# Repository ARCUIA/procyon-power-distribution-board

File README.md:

# procyon-power-distribution-board
Power distribution board responsible for managing power for the Atlas flight controller, up to 3 FPV camera + VTX systems, a radio module, and a DC motor. Toggle-able camera power to save battery. Support for High-side switching, allowing for chassis grounding on VTX modules.

### V1 Typical Application
- Battery: 2S LiPo 5000 mAh
- Flight Controller: Atlas V3
     - Input Voltage: 5V
     - Inpue Current (max): 250 mAh
- Motor: BLDC RS-380SH-4535
     - Input Voltage: 5V
     - Input Current: <1 amp
- Radio: RFD900X
     - Input Voltage: 5V
     - Input Current: 1 amp
- FPV Systems: CADDX Walksnail Avatar HD Pro
     - Input Voltage: Battery (Minimum 6V)
     - Input Current: 0.5-1 amp

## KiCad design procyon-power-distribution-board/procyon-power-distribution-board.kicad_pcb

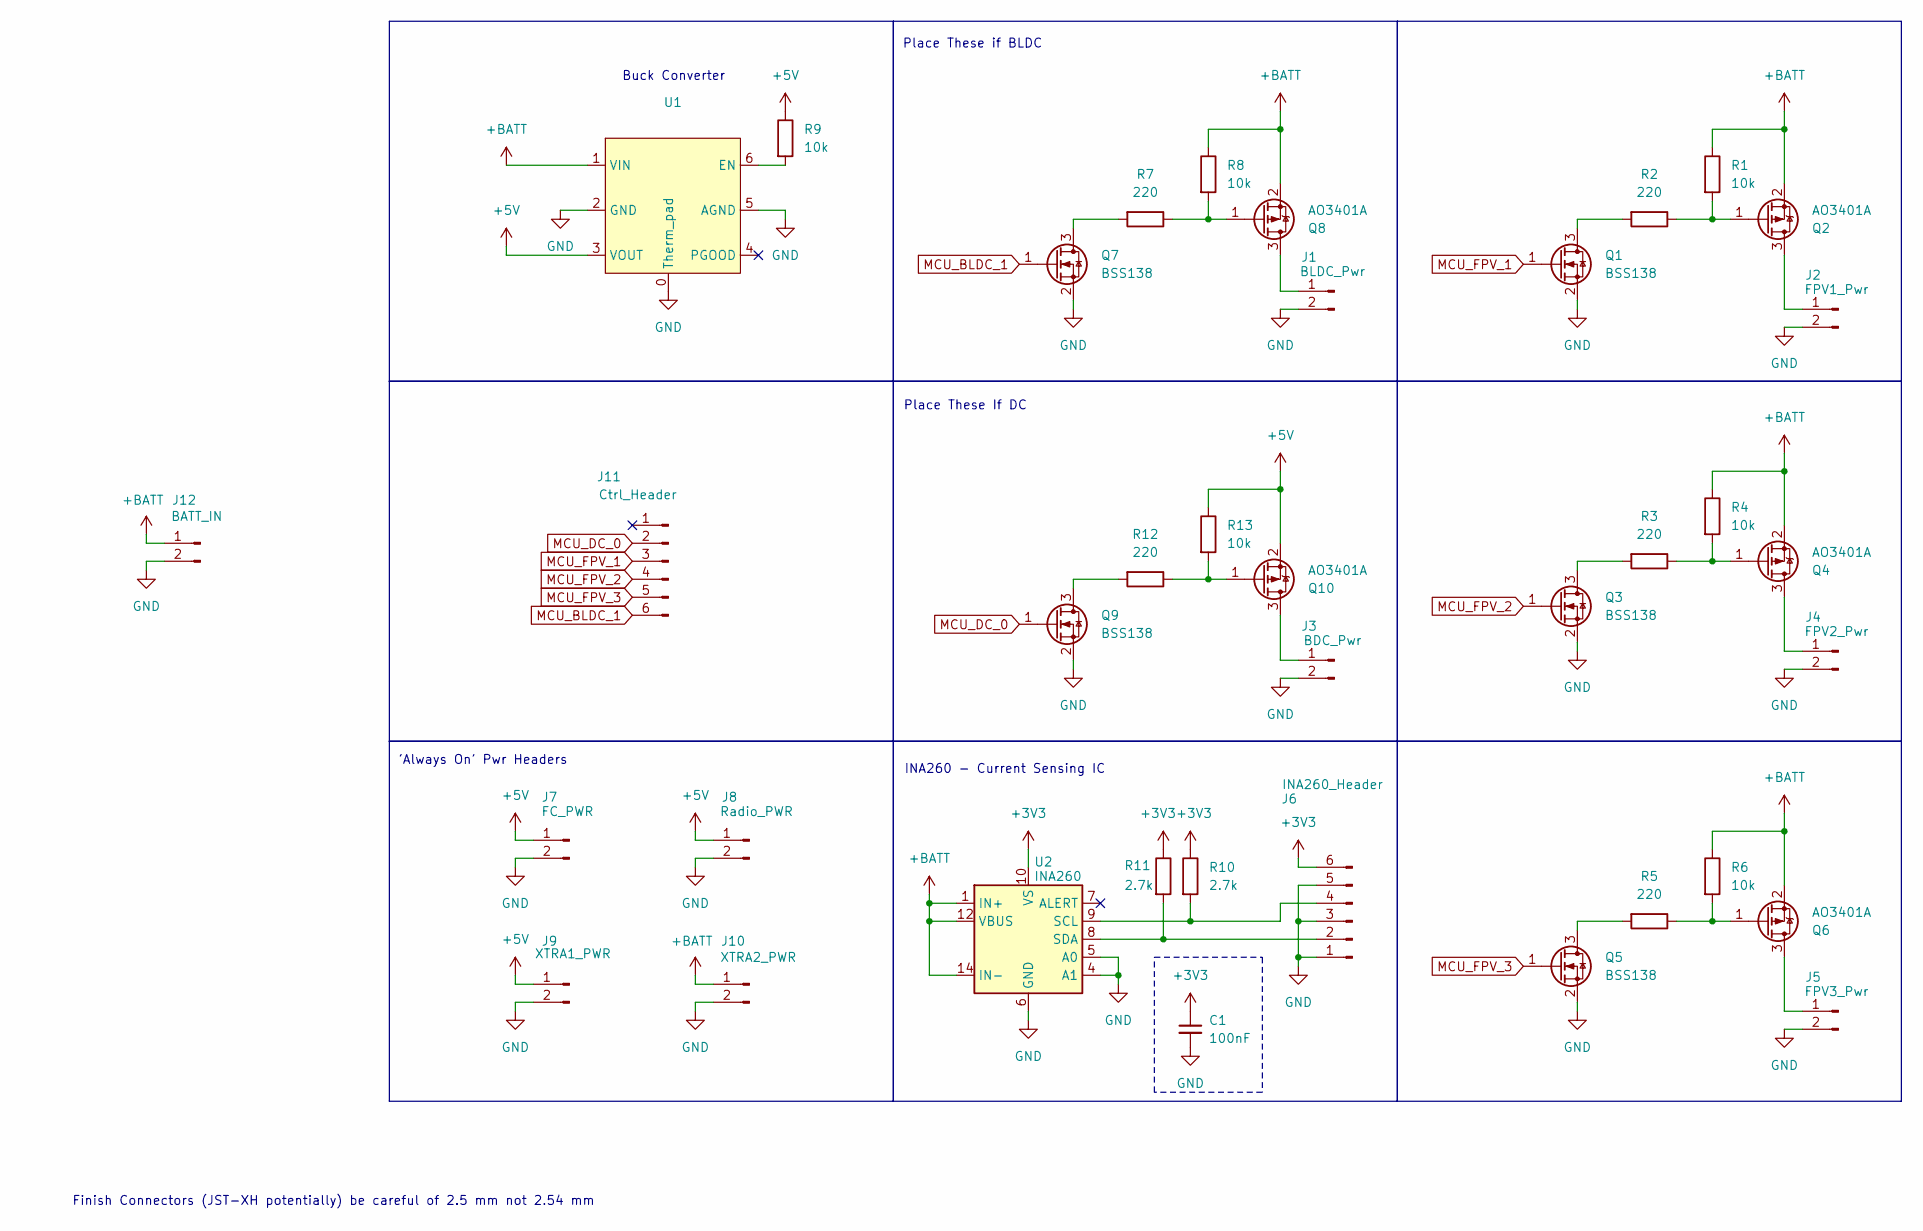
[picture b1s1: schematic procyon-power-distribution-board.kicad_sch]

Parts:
C1: 100nF; C_0603_1608Metric_Pad1.08x0.95mm_HandSolder
J1: BLDC_Pwr; JST_XH_S2B-XH-A-1_1x02_P2.50mm_Horizontal
J2: FPV1_Pwr; JST_XH_S2B-XH-A-1_1x02_P2.50mm_Horizontal
J3: BDC_Pwr; JST_XH_S2B-XH-A-1_1x02_P2.50mm_Horizontal
J4: FPV2_Pwr; JST_XH_S2B-XH-A-1_1x02_P2.50mm_Horizontal
J5: FPV3_Pwr; JST_XH_S2B-XH-A-1_1x02_P2.50mm_Horizontal
J6: INA260_Header; JST_XH_S6B-XH-A-1_1x06_P2.50mm_Horizontal
J7: FC_PWR; JST_XH_S2B-XH-A-1_1x02_P2.50mm_Horizontal
J8: Radio_PWR; JST_XH_S2B-XH-A-1_1x02_P2.50mm_Horizontal
J9: XTRA1_PWR; JST_XH_S2B-XH-A-1_1x02_P2.50mm_Horizontal
J10: XTRA2_PWR; JST_XH_S2B-XH-A-1_1x02_P2.50mm_Horizontal
J11: Ctrl_Header; JST_XH_S6B-XH-A-1_1x06_P2.50mm_Horizontal
J12: BATT_IN; SolderWire-1.5sqmm_1x02_P6mm_D1.7mm_OD3mm
Q1, Q3, Q5, Q7, Q9: BSS138; SOT-23
Q2, Q4, Q6, Q8, Q10: AO3401A; SOT-23
R1, R4, R6, R8, R9, R13: 10k; R_0603_1608Metric_Pad0.98x0.95mm_HandSolder
R2, R3, R5, R7, R12: 220; R_0603_1608Metric_Pad0.98x0.95mm_HandSolder
R10, R11: 2.7k; R_0603_1608Metric_Pad0.98x0.95mm_HandSolder
U1: CKCS_CK2416
U2: INA260; TSSOP-16_4.4x5mm_P0.65mm

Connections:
+3V3: C1.1, J6.6, R10.1, R11.1, U2.10 (VS)
+5V: J7.1, J8.1, J9.1, Q10.2 (S), R9.1, R13.1, U1.3 (VOUT)
+BATT: J10.1, J12.1, Q2.2 (S), Q4.2 (S), Q6.2 (S), Q8.2 (S), R1.1, R4.1, R6.1, R8.1, U1.1 (VIN), U2.1 (IN+), U2.2 (IN+), U2.3 (IN+), U2.12 (VBUS), U2.14 (IN-), U2.15 (IN-), U2.16 (IN-)
GND: C1.2, J1.2, J2.2, J3.2, J4.2, J5.2, J6.1, J6.3, J6.5, J7.2, J8.2, J9.2, J10.2, J12.2, Q1.2 (S), Q3.2 (S), Q5.2 (S), Q7.2 (S), Q9.2 (S), U1.0 (Therm_pad), U1.2 (GND), U1.5 (AGND), U2.4 (A1), U2.5 (A0), U2.6 (GND), U2.11 (GND)
MCU_BLDC_1: J11.6, Q7.1 (G)
MCU_DC_0: J11.2, Q9.1 (G)
MCU_FPV_1: J11.3, Q1.1 (G)
MCU_FPV_2: J11.4, Q3.1 (G)
MCU_FPV_3: J11.5, Q5.1 (G)
unnamed: J1.1, Q8.3 (D)
unnamed: J2.1, Q2.3 (D)
unnamed: J3.1, Q10.3 (D)
unnamed: J4.1, Q4.3 (D)
unnamed: J5.1, Q6.3 (D)
unnamed: J6.2, R11.2, U2.8 (SDA)
unnamed: J6.4, R10.2, U2.9 (SCL)
unnamed: Q1.3 (D), R2.2
unnamed: Q2.1 (G), R1.2, R2.1
unnamed: Q3.3 (D), R3.2
unnamed: Q4.1 (G), R3.1, R4.2
unnamed: Q5.3 (D), R5.2
unnamed: Q6.1 (G), R5.1, R6.2
unnamed: Q7.3 (D), R7.2
unnamed: Q8.1 (G), R7.1, R8.2
unnamed: Q9.3 (D), R12.2
unnamed: Q10.1 (G), R12.1, R13.2
unnamed: R9.2, U1.6 (EN)

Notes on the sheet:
Place These If DC
Finish Connectors (JST-XH potentially) be careful of 2.5 mm not 2.54 mm
Buck Converter
'Always On' Pwr Headers
INA260 - Current Sensing IC
Place These if BLDC

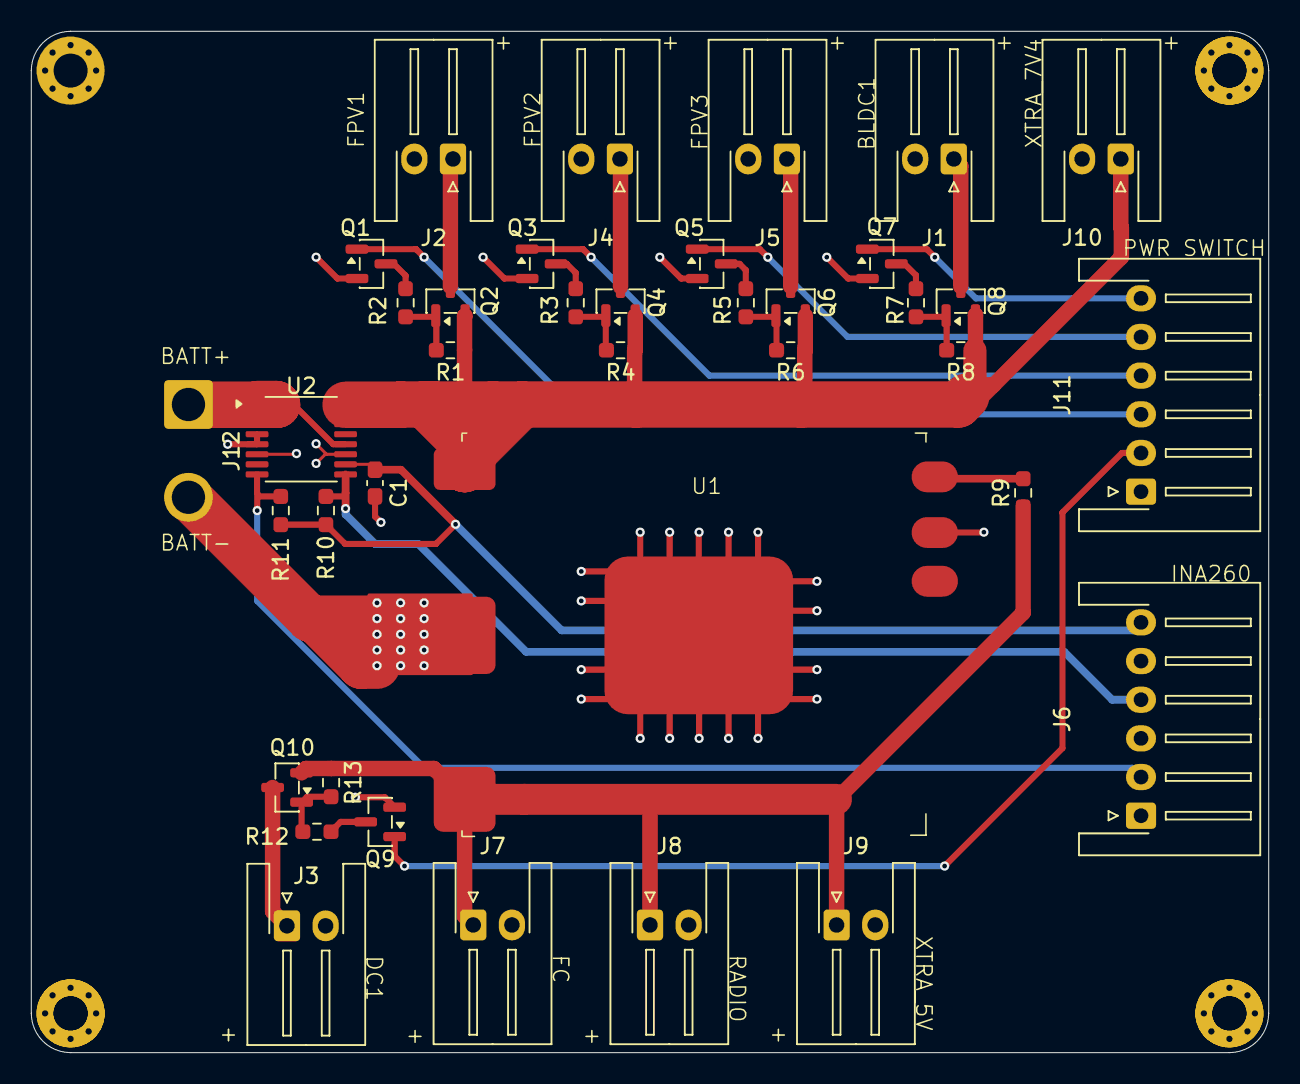
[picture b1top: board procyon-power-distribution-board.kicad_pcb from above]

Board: 4 copper layers, 80.0 x 66.0 mm, 38 parts (0 on the bottom side), 27 nets.

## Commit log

2026-03-29 Enhance README with application details and features
    Expanded description of power distribution board features and added typical application details.
2026-04-02 init commit
2026-04-02 layout 1 for mosfets
2026-04-02 added more structure. wip commit
2026-04-03 Mostly Done with Schematic. Need to wire up connectors (JST-XH???) and add some more filtering caps to the INA260
2026-04-06 Major changes, mostly finished, needs mounting holes and drc then finished.
2026-04-06 V1 DONE!
2026-04-06 adding STEP file for the MechEs
2026-04-06 adding production files
2026-04-06 random
2026-04-06 changed 3d model
